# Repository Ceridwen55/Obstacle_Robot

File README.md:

## 🤖 Wall Avoiding Robot (TM4C1294XL + PWM + Sharp IR Sensor)

A lightweight wall-avoiding robot built with the TM4C1294XL LaunchPad, using real analog sensor data and low-level embedded programming. No RTOS ( I dont think I need to implement this due to simple scheduling situation ), no Arduino. Just C, timers, ADCs, and PWM. Great for learning direct hardware control. I'm mixing DRM and TivaWare due to ADC RIS didn't work with my intention with using DRM only method, so that's that

---

## 🚀 Overview

The robot moves forward and avoids obstacles using two DC motors and two Sharp IR sensors. It reads distance on the left and right, calculates the error, and adjusts each motor's PWM speed to steer accordingly.

It uses:

- **SysTick timer** for generating PWM
- **ADC0 Sequencer 2** to read analog values from Sharp GP2Y0A21YK0F sensors (PE2 and PE3)
- **Bare-metal C programming** using TivaWare API
- **Empirical distance calibration formula** to convert ADC values into actual distance

---

## 📐 Core Logic

1. **PWM control using SysTick:**  
   Timer fires at 16 kHz. Each motor gets a PWM signal. PWM values are updated based on the sensor readings.

2. **Analog sensor readings (ADC):**  
   PE2 and PE3 (AIN1 and AIN0) are used for right and left distance sensors. ADC sequencer 2 reads both at once.

3. **Distance calculation:**  
   Distance (cm) = 114251 / ADC_Value
(Empirically derived constant for GP2Y0A21YK0F)

## Decision-making:
The difference between left and right distance determines motor speed difference. 

Logic:

If the robot is too close on one side → slow that side's motor

If both sides are balanced → move forward

## 🧠 Behavior Table

Condition	Action
error > 100	Turn left (slow right motor)
error < -100	Turn right (slow left motor)
-100 <= error <= 100	Move forward (equal speed)

## 📦 Hardware Bill of Materials (BoM)

| Component                        | Quantity | Notes                                      |
|----------------------------------|----------|--------------------------------------------|
| TM4C1294XL LaunchPad             | 1        | Main MCU board                             |
| DC Motors (3–7V, F130 type)      | 2        | For driving the wheels                     |
| Sharp IR Sensor (GP2Y0A21YK0F)   | 2        | Distance sensing front-left and front-right|
| IRLB3034 / TIP120 Transistors    | 2        | Motor driver (TIP120 used due to logic voltage compatibility) | ( *Yup this is too far right lol* )
| Diode 1N4002                     | 2        | Flyback protection                         |
| Capacitor 10µF                   | 2        | Noise filtering                            |
| L7805CV Voltage Regulator        | 1        | For 5V output to sensors & MCU             |
| Resistor 220Ω                    | 2        | Gate resistor for transistor               |
| Resistor 10kΩ                    | 2        | Pull-down on transistor gate               |
| LM2596 Buck Converter            | 1        | Optional for efficient power delivery      |
| Li-Ion Batteries (3.7V)          | 3        | Power source                               |
| Battery Holder (3-slot)          | 1        | For 3S battery configuration                |
| Robot chassis + wheels           | 1 set    | WD dual wheel kit or similar               |

## 🛠️ Software Highlights

- `PLL_Init()`  
Sets system clock to 120 MHz to allow fast ADC + PWM cycles

- `GPIOA_Init()`  
Initializes PA4 and PA5 as PWM-controlled motor outputs

- `GPIOE_Init()`  
Prepares PE2 and PE3 as analog inputs for the IR sensors

- `ADC0_Sequencer2_Init_SoftwareTrigger()`  
Uses Sequencer 2 with 2 steps to read both sensors

- `SysTick_Handler()`  
PWM generation and timing logic using hardware timer

- `Robot_Logic()`  
Core decision-making: steer left/right based on distance error

- `ADC_READ()`  
Read analog voltages, convert to digital values, apply distance formula

---

## 📏 Behavior

| Error Value (Right - Left) | Action                          |
|----------------------------|---------------------------------|
| > 100                      | Turn left (right slower)        |
| < -100                     | Turn right (left slower)        |
| -100 ≤ error ≤ 100         | Go straight (equal speed)       |

*Note: Values like `8200`, `6000`, etc. in SysTick PWM represent high-time portion out of 12000 total ticks (i.e., 60%, 50% duty cycle).*

---

## ⚙️ To-Do / Possible Improvements

- [ ] Stop completely if both distances are very short (e.g. wall directly ahead)
- [ ] Add LED indicators or debug UART for status reporting
- [ ] Add hysteresis for smoother turning
- [ ] Add PID-style control instead of simple threshold error
- [ ] VACUUMM CLEANERRRR
- [ ] Voice Assistant so at least I've got someone to talk when my Wife's working hehe ( I'm  going to make this cute robot on the next project using ESP32 instead so stay tuneee (I know this is hard but, LETS GOOO :))) )

---

## 🧪 Requirements

- TivaWare SDK
- ARM GCC or Code Composer Studio ( I'm using Keil uVision here )
- Due to DRM Method, it's exclusive on TM4C1294XL from Texas Instrument
- Soldering gear (if using PCB )
- Oscilloscope / logic analyzer (optional but useful, but I dont have one avail right now *cry*)

---

## 📷 Coming Soon

- Photos of the actual robot
- Short demo video
( You can see the project updates on my linkedin page here https://www.linkedin.com/in/muhammad-zaqzulkan/ )

---

## 💡 Inspiration

A mix of old-school analog robotics and low-level microcontroller programming ( honestly, it's Wall-E, really ). It’s a nice weekend project to brush up on embedded C, register-level config, and real-time logic. By the way, this is one of the first complex project that I'm just working on for my porto.

---

## 🛜 License

MIT License — free to use, modify, and share. If you build your own version or remix it, feel free to share back improvements ( I want to add another power source and a vacuum to be a vacuum cleaner robot due to my unbelievable laziness )

---

Thanks for checking out my simple project! Stay tune for my next project.

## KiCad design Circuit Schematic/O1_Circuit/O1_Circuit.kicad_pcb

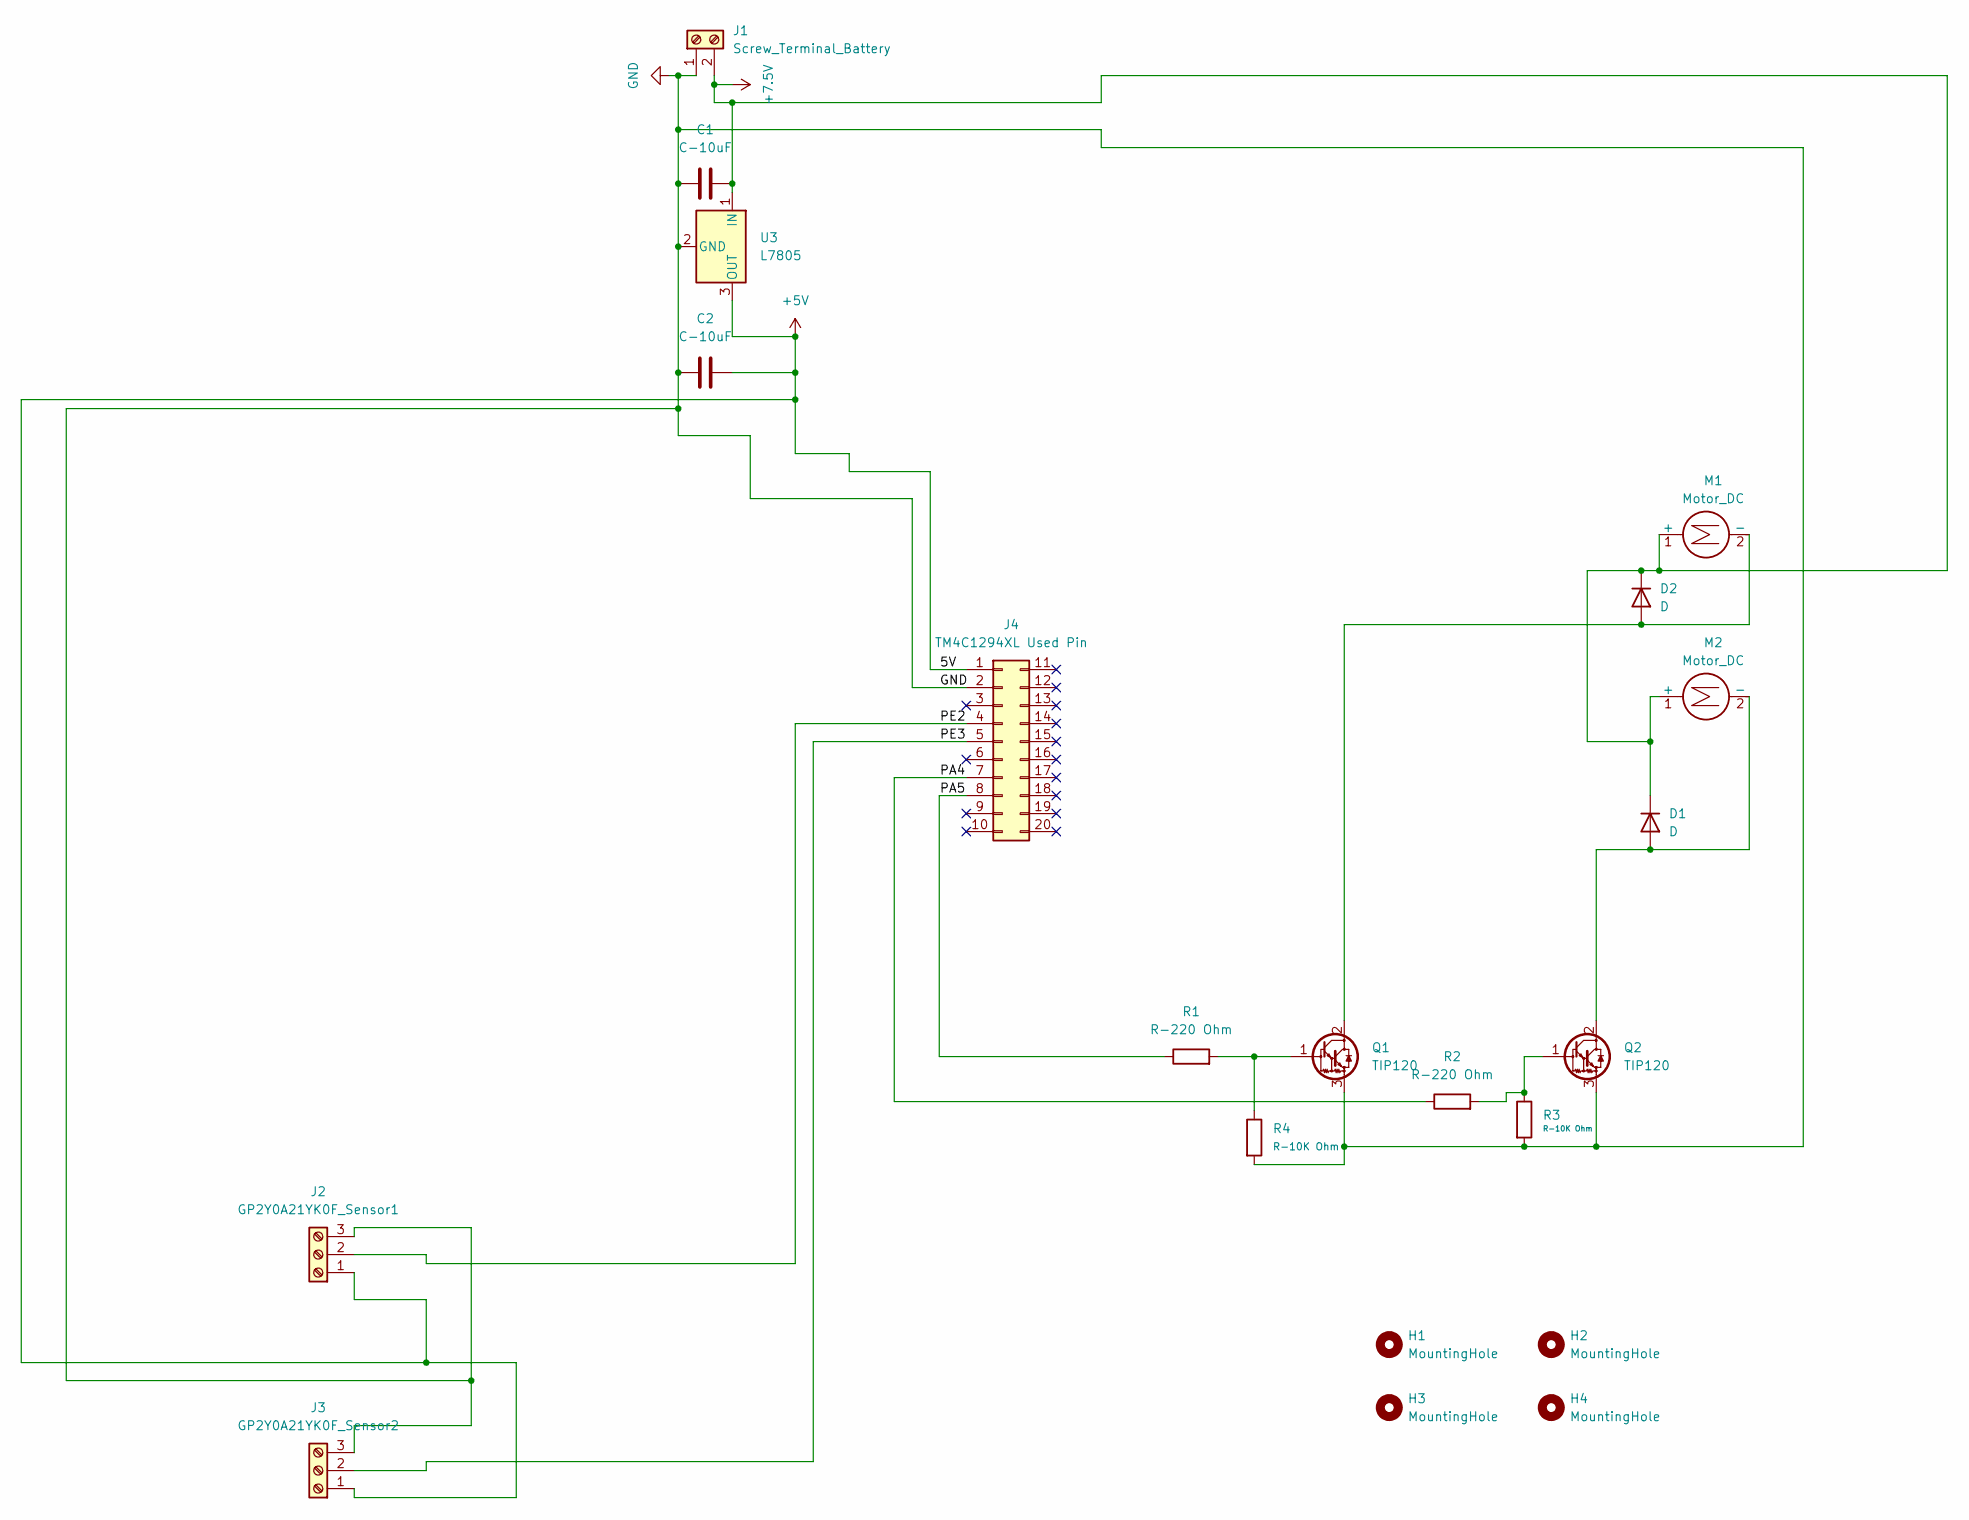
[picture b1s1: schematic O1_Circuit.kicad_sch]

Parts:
C1, C2: C-10uF; C_Disc_D7.5mm_W5.0mm_P5.00mm
D1, D2: D; D_A-405_P2.54mm_Vertical_AnodeUp
H1, H2, H3, H4: MountingHole; MountingHole_2.5mm
J1: Screw_Terminal_Battery; TerminalBlock_Phoenix_MKDS-3-2-5.08_1x02_P5.08mm_Horizontal
J2: GP2Y0A21YK0F_Sensor1; TerminalBlock_Phoenix_MKDS-3-3-5.08_1x03_P5.08mm_Horizontal
J3: GP2Y0A21YK0F_Sensor2; TerminalBlock_Phoenix_MKDS-3-3-5.08_1x03_P5.08mm_Horizontal
J4: TM4C1294XL Used Pin; PinHeader_2x10_P2.54mm_Vertical
M1, M2: Motor_DC; TerminalBlock_Phoenix_MKDS-3-2-5.08_1x02_P5.08mm_Horizontal
Q1, Q2: TIP120; TO-220-3_Vertical
R1, R2: R-220 Ohm; R_Axial_DIN0207_L6.3mm_D2.5mm_P7.62mm_Horizontal
R3, R4: R-10K Ohm; R_Axial_DIN0207_L6.3mm_D2.5mm_P7.62mm_Horizontal
U3: L7805; TO-220-3_Vertical

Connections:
+5V: C2.2, J2.1, J3.1, J4.1, U3.3 (OUT)
+7.5V: C1.2, D1.1 (K), D2.1 (K), J1.2, M1.1 (+), M2.1 (+), U3.1 (IN)
/PA4: J4.7, R2.1
/PA5: J4.8, R1.1
/PE2: J2.2, J4.4
/PE3: J3.2, J4.5
GND: C1.1, C2.1, J1.1, J2.3, J3.3, J4.2, Q1.3 (E), Q2.3 (E), R3.2, R4.2, U3.2 (GND)
unnamed: D1.2 (A), M2.2 (-), Q2.2 (C)
unnamed: D2.2 (A), M1.2 (-), Q1.2 (C)
unnamed: Q1.1 (B), R1.2, R4.1
unnamed: Q2.1 (B), R2.2, R3.1

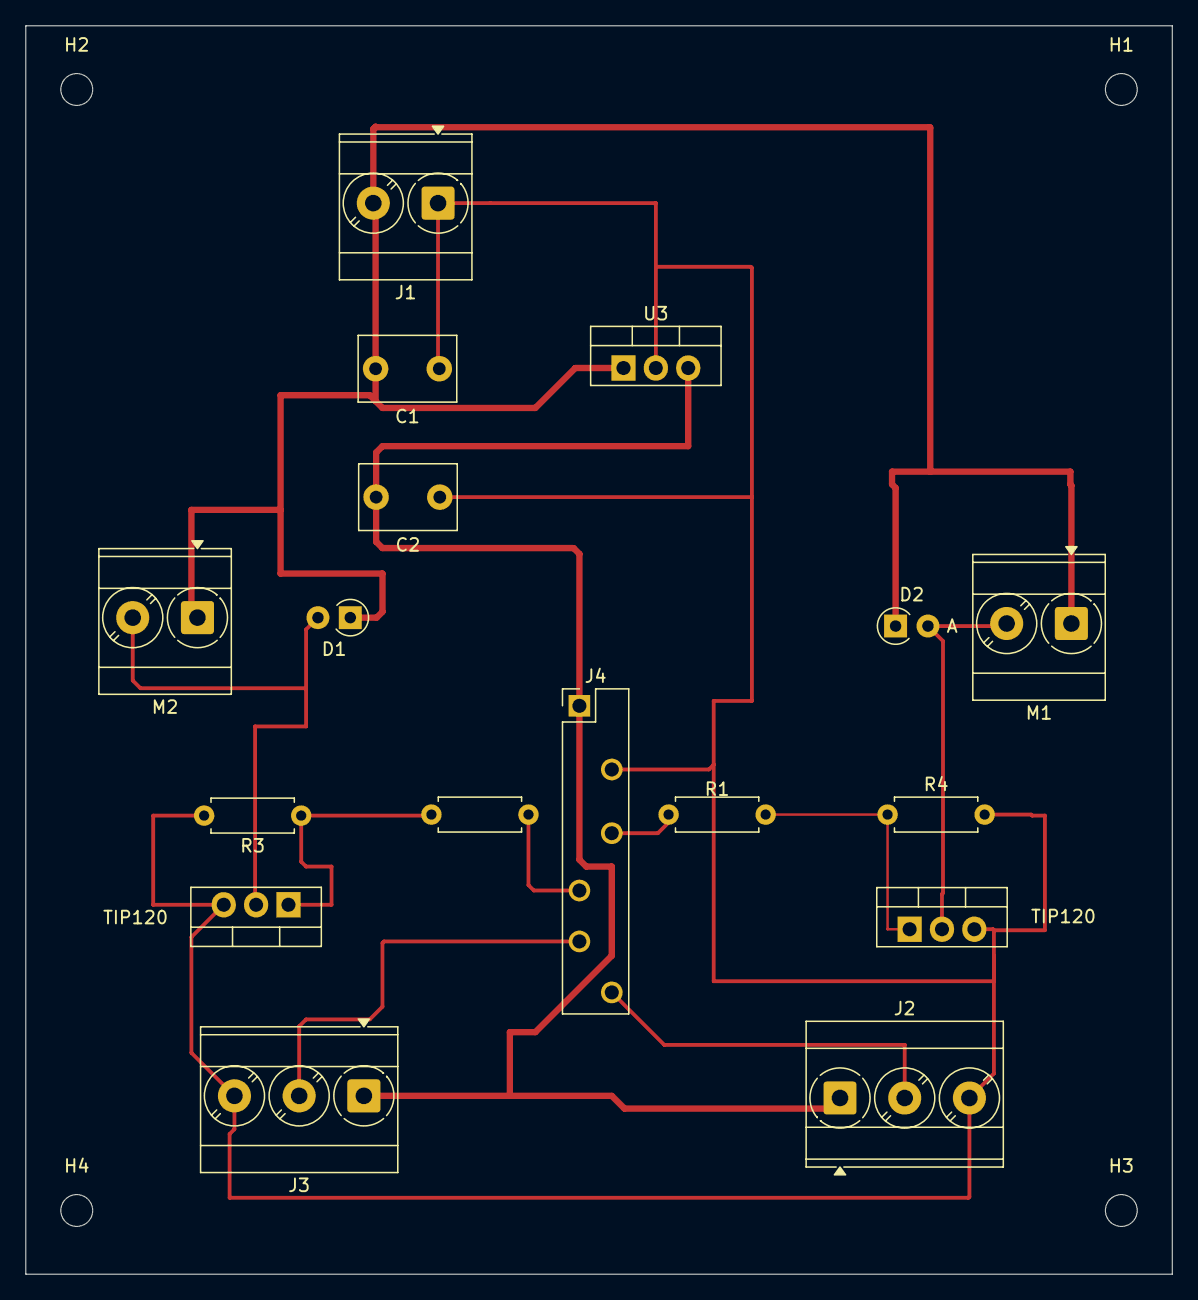
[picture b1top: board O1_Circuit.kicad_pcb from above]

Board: 2 copper layers, 90.0 x 98.0 mm, 21 parts (0 on the bottom side), 11 nets.

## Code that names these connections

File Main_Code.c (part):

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
/*

1. Set GPIO as the output to control 2 DC Motors ( 4-24 V ) (PA4 and PA5)

2. Set GPIO as the input from the distance sensors (Sharp GP2Y0A21YK0F) (Right now, PE3 and PE2 for AIN0 and AIN1)

3. Set the PWM function using Systick to automate and control the DC motors PWM
 - Using Systick to control the PWM at right and left DC motors
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{
	SYSCTL_RCGCGPIO_R |= 0x01;  //0000 0001 , turn on Port A clock
	while ((SYSCTL_RCGCGPIO_R & 0x01) == 0);
	GPIO_PORTA_DIR_R |= 0x30; //0011 0000, PA4 and PA5 as output
	GPIO_PORTA_DEN_R |= 0x30; //0011 0000, PA4 and PA5 use digital funct
	GPIO_PORTA_DR8R |= 0x30; //0011 0000, PA4 and PA5 has 8mA drive ( for dc motor amps)
	GPIO_PORTA_DATA_R &= ~0x30; //1100 1111, set PA4 and PA5 off so Systick Handler got benchmark on what to do next
}

void GPIOE_Init (void)
{
	SysCtlPeripheralEnable(SYSCTL_PERIPH_GPIOE); //0001 000"1", turn on port E clock yet not disturbing previous setup on Port A
  while (!SysCtlPeripheralReady(SYSCTL_PERIPH_GPIOE));
	GPIO_PORTE_DEN_R &= ~0x0C; // Disable digital PE2, PE3
	GPIO_PORTE_AFSEL_R |= 0x0C; // 0000 1100, PE3 and PE2 alternative funct on ( no need to setup dir cause already analog mode )
	GPIO_PORTE_AMSEL_R |= 0x0C; //0000 1100, PE3 and PE2 analog funct on
	
}

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   ADCSequenceDisable(ADC0_BASE, 2); //Disable seq2
   ADCSequenceConfigure(ADC0_BASE, 2, ADC_TRIGGER_PROCESSOR, 0);
   
   ADCSequenceStepConfigure(ADC0_BASE, 2, 0, ADC_CTL_CH1); // Step 0: AIN1 (PE2)
   
   ADCSequenceStepConfigure(ADC0_BASE, 2, 1, ADC_CTL_CH0 | ADC_CTL_IE | ADC_CTL_END); // Step 1: AIN0 (PE3) + IE + END

   ADCSequenceEnable(ADC0_BASE, 2); //Enable Seq 2
   ADCIntClear(ADC0_BASE, 2); // Clear
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	ADC0_SSPRI = 0x1023; // 1 for SS3, 0 for SS2, 2 for SS1, 3 for SS0. Smaller the number, higher the priority so SS2 is the highest
	ADC0_ACTSS &= ~0x04; //Disable Sample Sequencer 2 ( SS2)
	ADC0_EMUX &= ~0x0F00; //Software Trigger for seq 2
	ADC0_SSMUX2 = 0x01 | 0x00; //1 for AIN1 because PE2 at bit 0-3 at step 0, 0 for AIN0 because PE3 at bit 4-7 at step 1
	ADC0_SSCTL2 = 0x06 | 0x60; // IE0 and END0 for step 0 and IE1 and END1 for step 1
	ADC0_IM &= ~0x04; // disable interrupt mask for SS2
	ADC0_ACTSS |= 0x04; //enable sample sequencer 2 again
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   while (!ADCIntStatus(ADC0_BASE, 2, false));
   ADCSequenceDataGet(ADC0_BASE, 2, adc_vals);
   ADCIntClear(ADC0_BASE, 2);
	 sensor_value[0] = adc_vals[0]; // PE2 converted distance
   sensor_value[1] = adc_vals[1]; // PE3 converted distance

	
	
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
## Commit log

2025-06-18 Adding Project's Spec
2025-06-18 Adding hardware BOM part 1
2025-06-19 Finishing on setting the addresses
2025-06-20 Init GPIO A and E done
2025-06-20 Finishing on init ADC0
2025-06-20 Adding Systick Init
2025-06-21 Finishing setting up ADC sampling
2025-06-21 General logic funct is ready
2025-06-22 Experimenting with independent PWM
2025-06-23 Polishing the functions
2025-06-26 Progressing on schematic
2025-06-26 Almost finished with Schematic
2025-07-02 Begin Prototyping
2025-07-07 Hybrid using API TivaWare Due to ADC error DRM
2025-07-14 Hybrid with TivaWare API due to error ADC
2025-07-14 Correcting Logic
2025-07-21 Fixing Schematic and Start desigbing PCB
2025-07-23 Fiishing PCB
2025-07-23 Touch up PCB
2025-07-29 PCB Design Edit
2025-08-02 Editing PCB due to short on prev
2025-08-04 Calibrating Distance Sensor Obstacle Detection
2025-08-04 Create README.md
    Early Description Of The Project
2025-08-04 Update README.md
    Editing
2025-08-04 Tidying Up
